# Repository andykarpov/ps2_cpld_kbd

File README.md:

# PS/2 AVR CPLD keyboard adapter

PS/2 keyboard adapter for ZX Spectrum on Atmega328 + EPM7128STC100.
Designed to be connected directly instead of a mechanical keyboard.

Based on the idea of the Yet another ZX-Spectrum AT Keyboard Interface http://www.jrok.com/project/speckey/spec_key.html

## How to program

### Programming Atmega328p
1. disconnect EPM7128 from the power source by disconnecting jumper JP1
2. avrdude -p atmega328p -c USBasp -U flash:w:avr_kbd_mega328p.hex -U lfuse:w:0xbf:m -U hfuse:w:0xda:m -U efuse:w:0xfd:m
3. short JP1

### Programming EPM7128S
use quartus programmer to flash cpld_kbd.pof

## Available hotkeys
1. Ctrl+Alt+Del generate a short negative pulse on O_RESET pin. It's nice to connect this signal to N_RESET of your ZX Spectrum
2. Ctrl+Alt+Backspace produce a controller internal reset needed for some reason
3. F2 generate a short negative pulse on O_MAGICK pin. If you have a BDI controller then you have to connect this signal to magick button.
4. Scroll Lock switch on / off the O_TURBO signal
5. PrintScreen switch on / off the O_SPECIAL signal

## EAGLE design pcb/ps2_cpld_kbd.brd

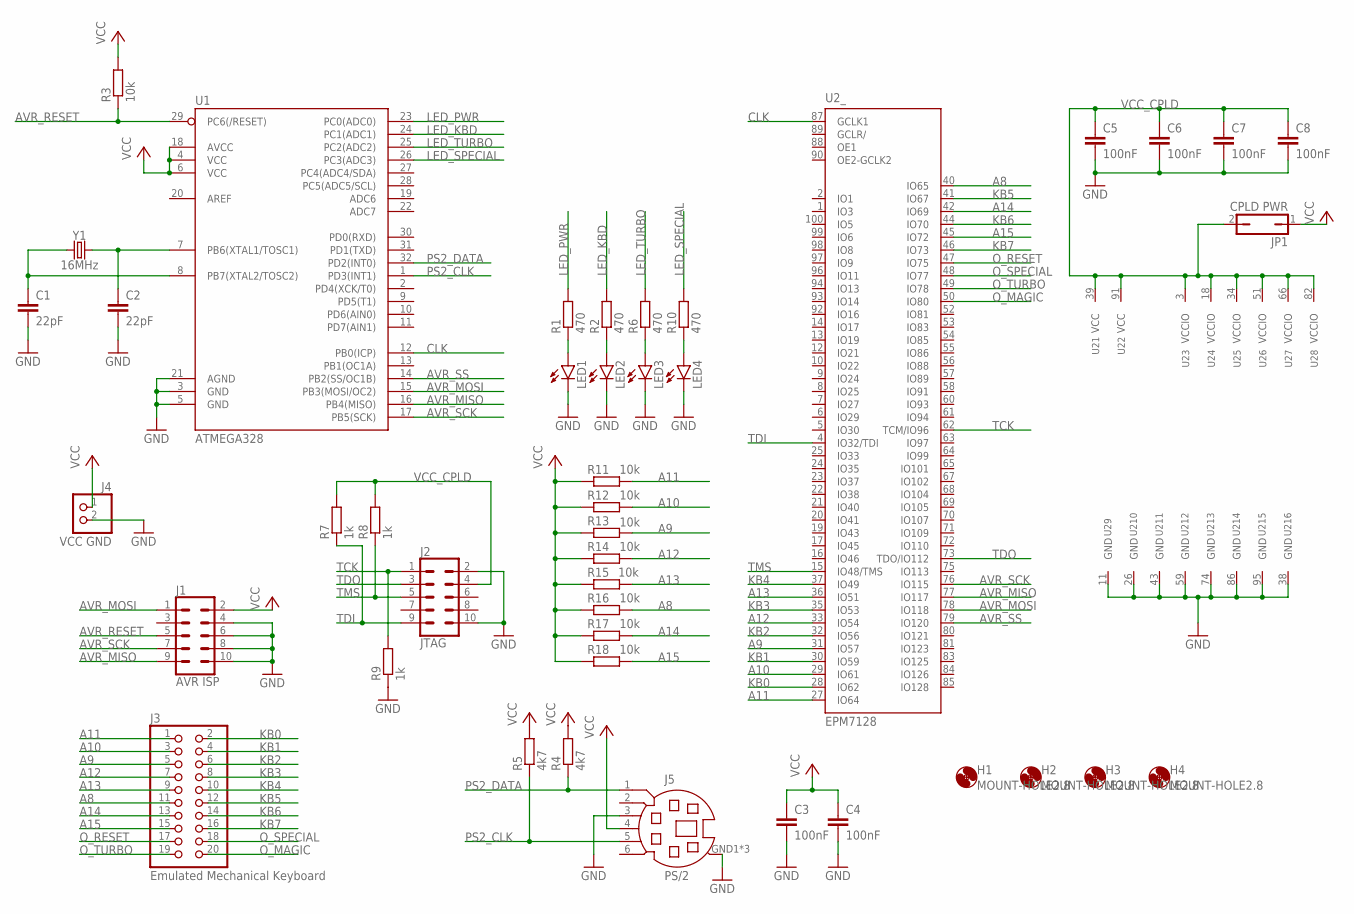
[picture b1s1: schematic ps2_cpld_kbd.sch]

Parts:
C1, C2: 22pF; C0805K
C3, C4, C5, C6, C7, C8: 100nF; C0805K
H1, H2, H3, H4: MOUNT-HOLE2.8; 2,8
J1: AVR ISP; 2X5-SHROUDED_LOCK
J2: JTAG; 2X5-SHROUDED_LOCK
J3: Emulated Mechanical Keyboard; 2X10
J4: VCC GND; 1X02
J5: PS/2; MDIN06SS
JP1: CPLD PWR; JP1
LED1, LED2, LED3, LED4: LEDCHIPLED_0805; CHIPLED_0805
R1, R2, R6, R10: 470; R0805
R3, R11, R12, R13, R14, R15, R16, R17, R18: 10k; R0805
R4, R5: 4k7; R0805
R7, R8, R9: 1k; R0805
U1: ATMEGA328; TQFP32-08
U2: EPM7128; TQFP100
Y1: 16MHz; HC49US

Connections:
A8: J3.11, R16.2, U2.40 (IO65)
A9: J3.5, R13.2, U2.31 (IO57)
A10: J3.3, R12.2, U2.29 (IO61)
A11: J3.1, R11.2, U2.27 (IO64)
A12: J3.7, R14.2, U2.33 (IO54)
A13: J3.9, R15.2, U2.36 (IO51)
A14: J3.13, R17.2, U2.42 (IO69)
A15: J3.15, R18.2, U2.45 (IO72)
AVR_MISO: J1.9, U1.16 (PB4(MISO)), U2.77 (IO117)
AVR_MOSI: J1.1, U1.15 (PB3(MOSI/OC2)), U2.78 (IO118)
AVR_RESET: J1.5, R3.1, U1.29 (PC6(/RESET))
AVR_SCK: J1.7, U1.17 (PB5(SCK)), U2.76 (IO115)
AVR_SS: U1.14 (PB2(SS/OC1B)), U2.79 (IO120)
CLK: U1.12 (PB0(ICP)), U2.87 (GCLK1)
GND: C1.2, C2.2, C3.2, C4.2, C5.2, C6.2, C7.2, C8.2, J1.4, J1.6, J1.8, J1.10, J2.2, J2.10, J4.2, J5.3, J5.GND1 (GND), J5.GND2 (GND), J5.GND3 (GND), LED1.C, LED2.C, LED3.C, LED4.C, R9.1, U1.3 (GND), U1.5 (GND), U1.21 (AGND), U2.11 (GND), U2.26 (GND), U2.38 (GND), U2.43 (GND), U2.59 (GND), U2.74 (GND), U2.86 (GND), U2.95 (GND)
KB0: J3.2, U2.28 (IO62)
KB1: J3.4, U2.30 (IO59)
KB2: J3.6, U2.32 (IO56)
KB3: J3.8, U2.35 (IO53)
KB4: J3.10, U2.37 (IO49)
KB5: J3.12, U2.41 (IO67)
KB6: J3.14, U2.44 (IO70)
KB7: J3.16, U2.46 (IO73)
LED_KBD: R2.2, U1.24 (PC1(ADC1))
LED_PWR: R1.2, U1.23 (PC0(ADC0))
LED_SPECIAL: R10.2, U1.26 (PC3(ADC3))
LED_TURBO: R6.2, U1.25 (PC2(ADC2))
unnamed: LED3.A, R6.1
unnamed: LED2.A, R2.1
unnamed: LED1.A, R1.1
unnamed: C2.1, U1.7 (PB6(XTAL1/TOSC1)), Y1.2
unnamed: C1.1, U1.8 (PB7(XTAL2/TOSC2)), Y1.1
unnamed: LED4.A, R10.1
O_MAGIC: J3.20, U2.50 (IO80)
O_RESET: J3.17, U2.47 (IO75)
O_SPECIAL: J3.18, U2.48 (IO77)
O_TURBO: J3.19, U2.49 (IO78)
PS2_CLK: J5.5, R5.1, U1.1 (PD3(INT1))
PS2_DATA: J5.1, R4.1, U1.32 (PD2(INT0))
TCK: J2.1, R9.2, U2.62 (TCM/IO96)
TDI: J2.9, R7.1, U2.4 (IO32/TDI)
TDO: J2.3, U2.73 (TDO/IO112)
TMS: J2.5, R8.1, U2.15 (IO48/TMS)
VCC: C3.1, C4.1, J1.2, J4.1, J5.4, JP1.1, R3.2, R4.2, R5.2, R11.1, R12.1, R13.1, R14.1, R15.1, R16.1, R17.1, R18.1, U1.4 (VCC), U1.6 (VCC), U1.18 (AVCC)
VCC_CPLD: C5.1, C6.1, C7.1, C8.1, J2.4, JP1.2, R7.2, R8.2, U2.3 (VCCIO), U2.18 (VCCIO), U2.34 (VCCIO), U2.39 (VCC), U2.51 (VCCIO), U2.66 (VCCIO), U2.82 (VCCIO), U2.91 (VCC)

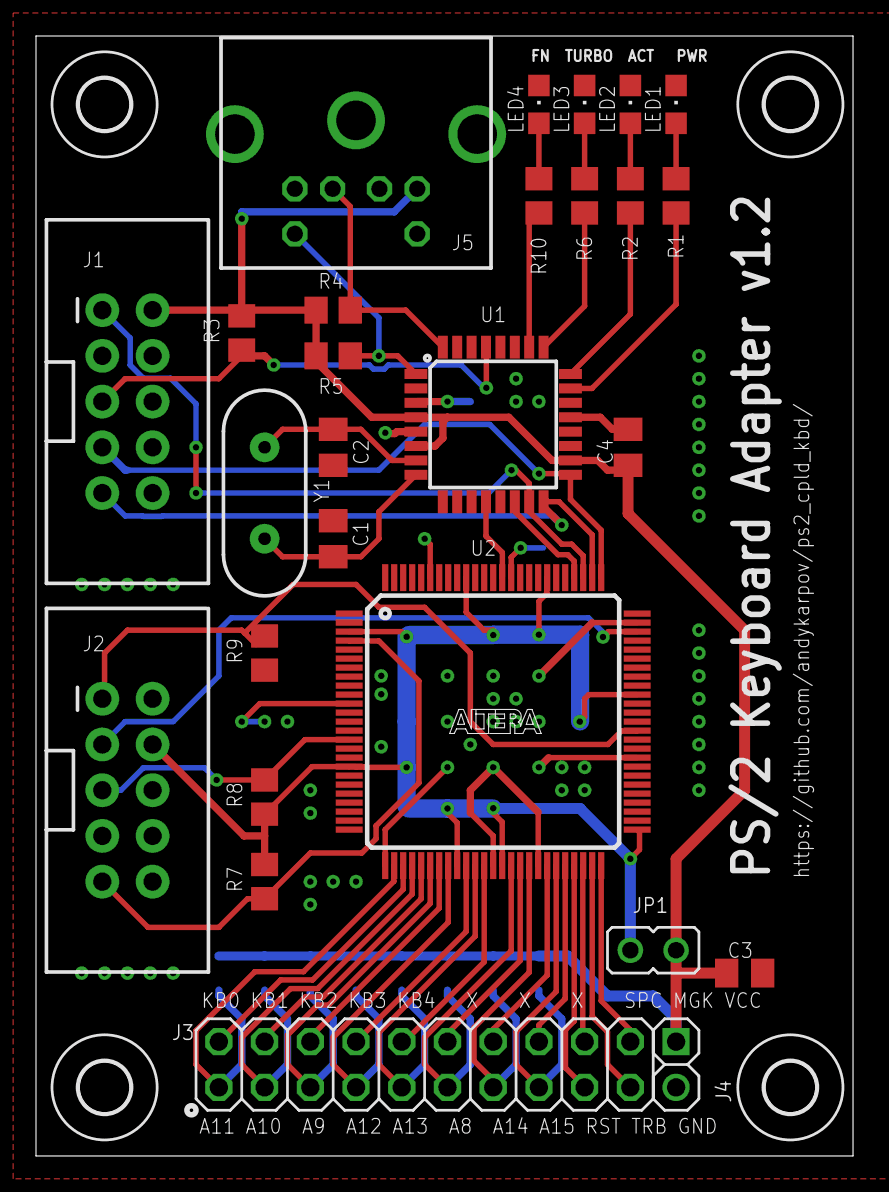
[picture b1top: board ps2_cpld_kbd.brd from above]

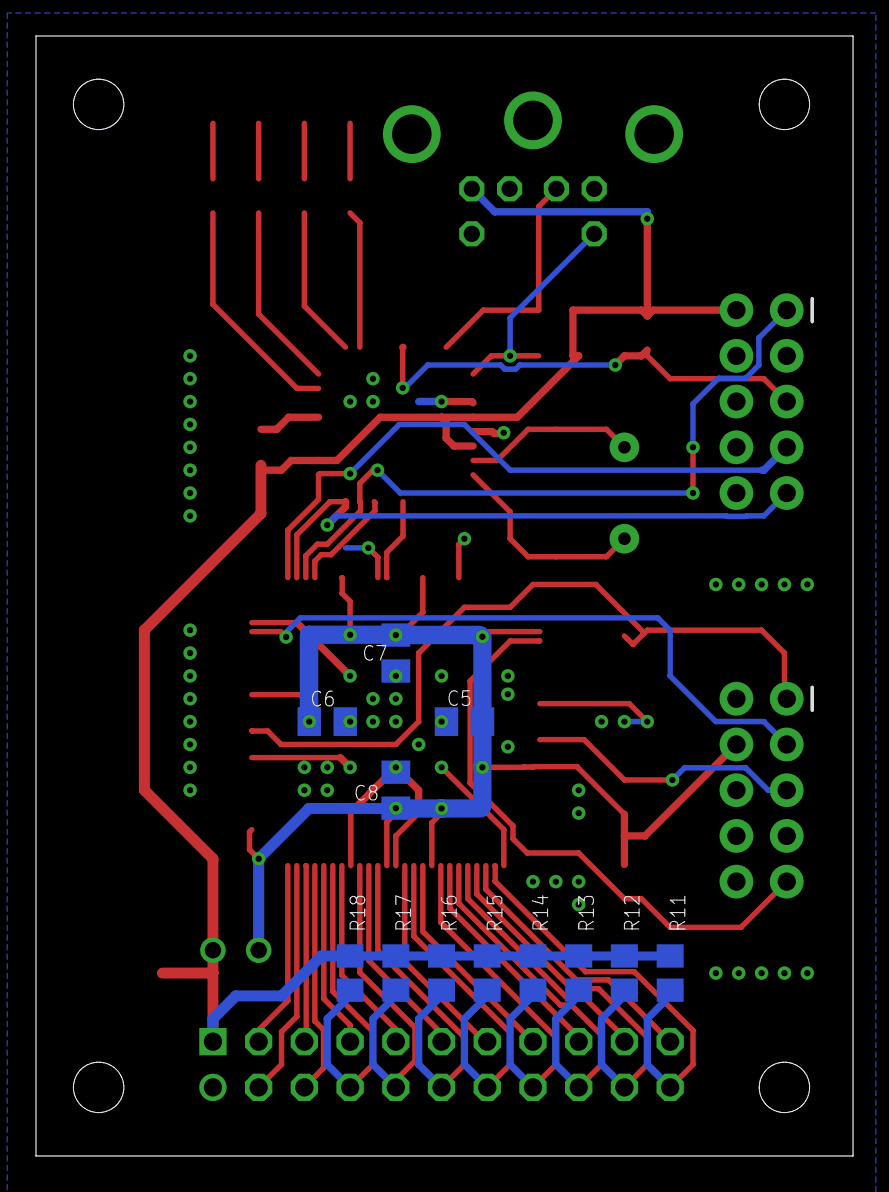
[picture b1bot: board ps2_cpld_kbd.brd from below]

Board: 2 copper layers, 45.4 x 62.2 mm, 43 parts (12 on the bottom side), 45 nets.

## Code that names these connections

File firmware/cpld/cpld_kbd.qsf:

# -------------------------------------------------------------------------- #
#
# Copyright (C) 1991-2013 Altera Corporation
# Your use of Altera Corporation's design tools, logic functions 
# and other software and tools, and its AMPP partner logic 
# functions, and any output files from any of the foregoing 
# (including device programming or simulation files), and any 
# associated documentation or information are expressly subject 
# to the terms and conditions of the Altera Program License 
# Subscription Agreement, Altera MegaCore Function License 
# Agreement, or other applicable license agreement, including, 
# without limitation, that your use is for the sole purpose of 
# programming logic devices manufactured by Altera and sold by 
# Altera or its authorized distributors.  Please refer to the 
# applicable agreement for further details.
#
# -------------------------------------------------------------------------- #
#
# Quartus II 32-bit
# Version 13.1.0 Build 162 10/23/2013 SJ Web Edition
# Date created = 14:53:04  января 06, 2019
#
# -------------------------------------------------------------------------- #
#
# Notes:
#
# 1) The default values for assignments are stored in the file:
#		cpld_kbd_assignment_defaults.qdf
#    If this file doesn't exist, see file:
#		assignment_defaults.qdf
#
# 2) Altera recommends that you do not modify this file. This
#    file is updated automatically by the Quartus II software
#    and any changes you make may be lost or overwritten.
#
# -------------------------------------------------------------------------- #


set_global_assignment -name TOP_LEVEL_ENTITY cpld_kbd
set_global_assignment -name VHDL_FILE spi_slave.vhd
set_global_assignment -name VHDL_FILE cpld_kbd.vhd

set_location_assignment PIN_87 -to CLK
set_location_assignment PIN_37 -to KB[4]
set_location_assignment PIN_35 -to KB[3]
set_location_assignment PIN_32 -to KB[2]
set_location_assignment PIN_30 -to KB[1]
set_location_assignment PIN_28 -to KB[0]
set_location_assignment PIN_36 -to A[13]
set_location_assignment PIN_33 -to A[12]
set_location_assignment PIN_31 -to A[9]
set_location_assignment PIN_29 -to A[10]
set_location_assignment PIN_27 -to A[11]
set_location_assignment PIN_40 -to A[8]
set_location_assignment PIN_42 -to A[14]
set_location_assignment PIN_45 -to A[15]
set_location_assignment PIN_77 -to AVR_MISO
set_location_assignment PIN_78 -to AVR_MOSI
set_location_assignment PIN_76 -to AVR_SCK
set_location_assignment PIN_79 -to AVR_SS
set_location_assignment PIN_50 -to O_MAGICK
set_location_assignment PIN_49 -to O_TURBO
set_location_assignment PIN_48 -to O_SPECIAL
set_location_assignment PIN_47 -to O_RESET


set_global_assignment -name FAMILY MAX7000S
set_global_assignment -name DEVICE "EPM7128STC100-15"
set_global_assignment -name ORIGINAL_QUARTUS_VERSION "13.0 SP1"
set_global_assignment -name PROJECT_CREATION_TIME_DATE "11:31:59  SEPTEMBER 25, 2017"
set_global_assignment -name LAST_QUARTUS_VERSION "13.0 SP1"
set_global_assignment -name DEVICE_FILTER_PIN_COUNT 100
set_global_assignment -name ERROR_CHECK_FREQUENCY_DIVISOR "-1"
set_global_assignment -name EDA_SIMULATION_TOOL "ModelSim-Altera (VHDL)"
set_global_assignment -name EDA_OUTPUT_DATA_FORMAT VHDL -section_id eda_simulation
set_global_assignment -name MAX7000_DEVICE_IO_STANDARD TTL

set_global_assignment -name FMAX_REQUIREMENT "16 MHz"
set_global_assignment -name FMAX_REQUIREMENT "16 MHz" -section_id CLK
set_global_assignment -name MAX7000_OPTIMIZATION_TECHNIQUE BALANCED
set_global_assignment -name AUTO_LCELL_INSERTION ON
set_global_assignment -name OPTIMIZE_HOLD_TIMING OFF
set_global_assignment -name AUTO_GLOBAL_CLOCK_MAX ON
set_global_assignment -name AUTO_GLOBAL_OE_MAX ON
set_global_assignment -name MAX_AUTO_GLOBAL_REGISTER_CONTROLS ON
set_instance_assignment -name CLOCK_SETTINGS CLK -to CLK
set_global_assignment -name FIT_ONLY_ONE_ATTEMPT OFF
set_global_assignment -name SIMULATION_MODE FUNCTIONAL
set_global_assignment -name RESERVE_ALL_UNUSED_PINS_NO_OUTPUT_GND "AS INPUT TRI-STATED"
set_global_assignment -name OPTIMIZE_IOC_REGISTER_PLACEMENT_FOR_TIMING NORMAL
set_global_assignment -name AUTO_TURBO_BIT AUTO
set_global_assignment -name REMOVE_DUPLICATE_REGISTERS ON
set_global_assignment -name AUTO_RESOURCE_SHARING ON
set_global_assignment -name STRATIXII_OPTIMIZATION_TECHNIQUE AREA
set_global_assignment -name CYCLONE_OPTIMIZATION_TECHNIQUE AREA
set_global_assignment -name STRATIX_OPTIMIZATION_TECHNIQUE AREA
set_global_assignment -name MAXII_OPTIMIZATION_TECHNIQUE AREA
set_global_assignment -name APEX20K_OPTIMIZATION_TECHNIQUE AREA
set_global_assignment -name STATE_MACHINE_PROCESSING "MINIMAL BITS"
set_global_assignment -name MAX7000_FANIN_PER_CELL 100
set_global_assignment -name DO_MIN_ANALYSIS OFF
set_global_assignment -name CUT_OFF_PATHS_BETWEEN_CLOCK_DOMAINS ON
set_global_assignment -name CUT_OFF_READ_DURING_WRITE_PATHS ON
set_global_assignment -name CUT_OFF_IO_PIN_FEEDBACK ON
set_global_assignment -name BLOCK_DESIGN_NAMING MAXPLUSII
set_global_assignment -name MAX7000_PARALLEL_EXPANDER_CHAIN_LENGTH 2
set_global_assignment -name SUPPRESS_REG_MINIMIZATION_MSG ON
set_global_assignment -name ENABLE_DRC_SETTINGS ON


set_global_assignment -name SYNTH_TIMING_DRIVEN_SYNTHESIS OFF
set_global_assignment -name OPTIMIZE_MULTI_CORNER_TIMING ON
set_global_assignment -name FITTER_EFFORT "STANDARD FIT"
set_global_assignment -name ALM_REGISTER_PACKING_EFFORT MEDIUM
set_global_assignment -name ECO_OPTIMIZE_TIMING OFF
set_global_assignment -name ECO_REGENERATE_REPORT OFF
set_global_assignment -name SLOW_SLEW_RATE OFF
set_global_assignment -name FORCE_FITTER_TO_AVOID_PERIPHERY_PLACEMENT_WARNINGS OFF


set_location_assignment PIN_46 -to O_CLK
set_location_assignment PIN_44 -to O_TEST
set_location_assignment PIN_41 -to O_DEBUG

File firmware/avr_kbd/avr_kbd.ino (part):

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#define DEBUG_MODE 0

// ---- Pins for Atmega328
#define PIN_KBD_CLK 3 // PD2
#define PIN_KBD_DAT 2 // PD2

// hardware SPI
#define PIN_SS 10 // SPI slave select

#define LED_PWR A0
#define LED_KBD A1
#define LED_TURBO A2
#define LED_SPECIAL A3

#define EEPROM_TURBO_ADDRESS 0x00
#define EEPROM_SPECIAL_ADDRESS 0x01
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  pinMode(PIN_SS, OUTPUT);
  digitalWrite(PIN_SS, HIGH);

  pinMode(LED_PWR, OUTPUT);
  pinMode(LED_KBD, OUTPUT);
  pinMode(LED_TURBO, OUTPUT);
  pinMode(LED_SPECIAL, OUTPUT);
  
  digitalWrite(LED_PWR, HIGH);
  digitalWrite(LED_KBD, HIGH);
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
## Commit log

2019-03-05 Added eagle sources and gerbers
2019-03-05 added avr firmware
2019-03-05 cpld firmware added
2019-03-05 added firmware binaries
2019-03-06 removed atmega8 hex because it does not support CKOUT
2019-03-13 fixed ps2 pin mapping
2019-03-13 added debug signals output
2019-03-13 fixed ps/2 signal names, fixed github page url
2019-03-13 updated schamatics and board v1.1
2019-03-13 pcb gerbers v1.1
2019-03-13 modified cam processor job
2019-03-13 new board v1.2 with fixes
2019-03-13 added schematic diagram
2019-03-14 fixed bugs with external signals O_RESET & co
2019-03-17 pcb photo v1.2
2019-03-17 new real photo
2019-03-18 added legacy gerbers (seed fusion cam job)
2019-07-13 fixed issue with shift special keys
2019-07-13 new release
2019-07-13 Implemented macroses for special keys, like [, ], {, }, ~, `
2020-03-06 added BOM
2020-05-20 Addded Z-state to the KB output to avoid intersection with a physical keyboard

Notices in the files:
parts and their libraries:
SparkFun-IC-Microcontroller: Licensing: Creative Commons ShareAlike 4.0 International - https://creativecommons.org/licenses/by-sa/4.0
